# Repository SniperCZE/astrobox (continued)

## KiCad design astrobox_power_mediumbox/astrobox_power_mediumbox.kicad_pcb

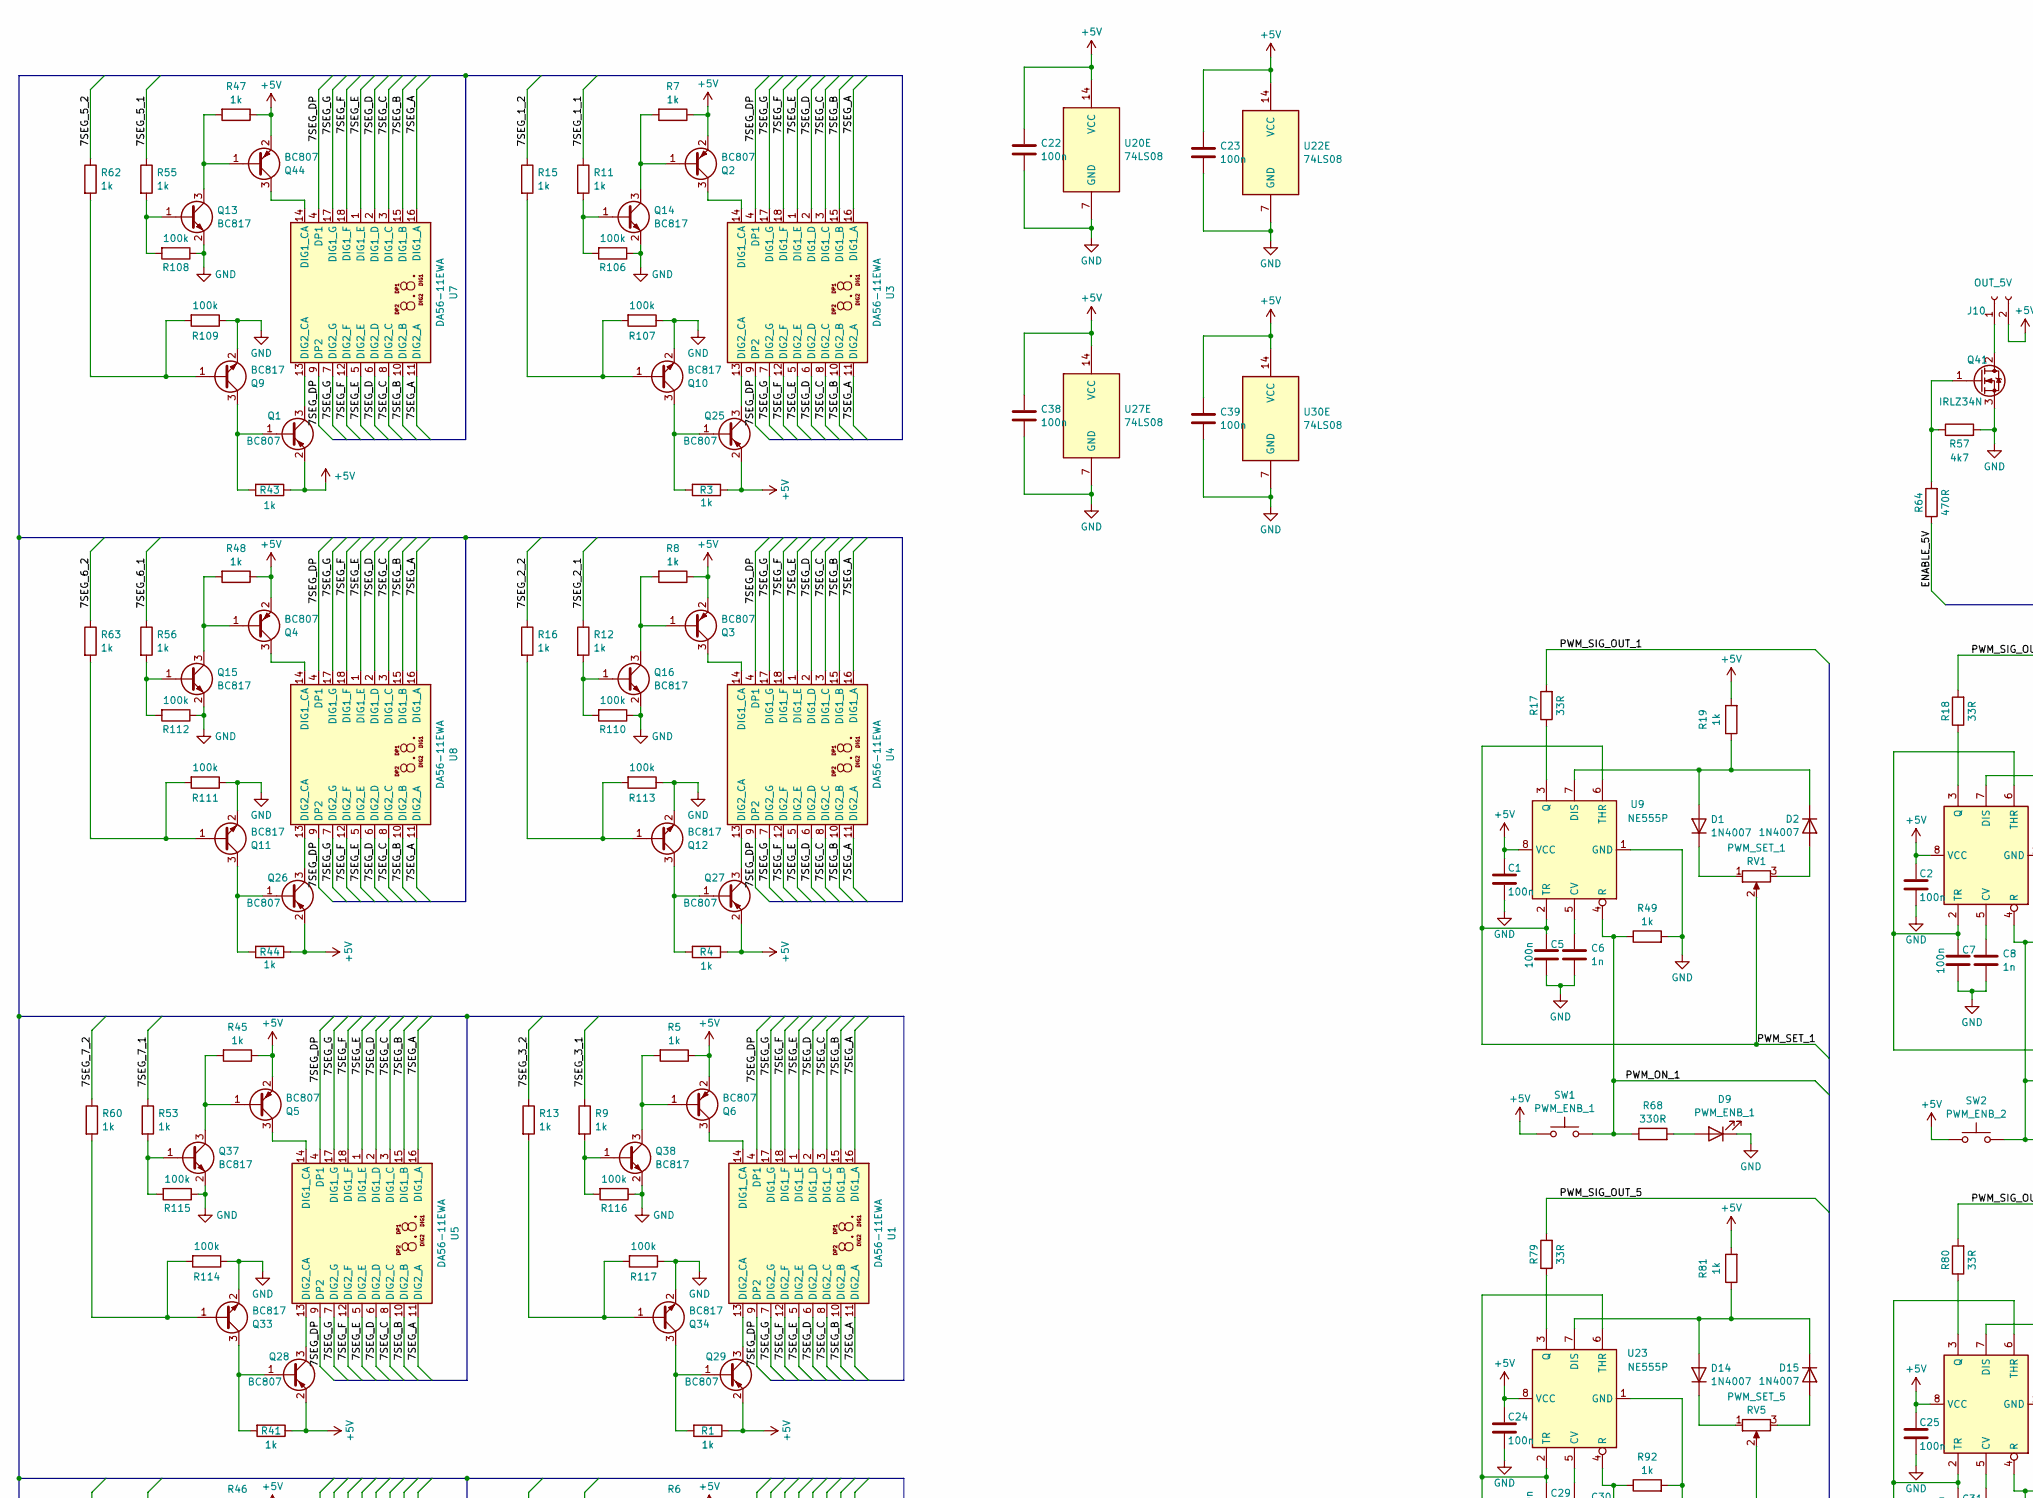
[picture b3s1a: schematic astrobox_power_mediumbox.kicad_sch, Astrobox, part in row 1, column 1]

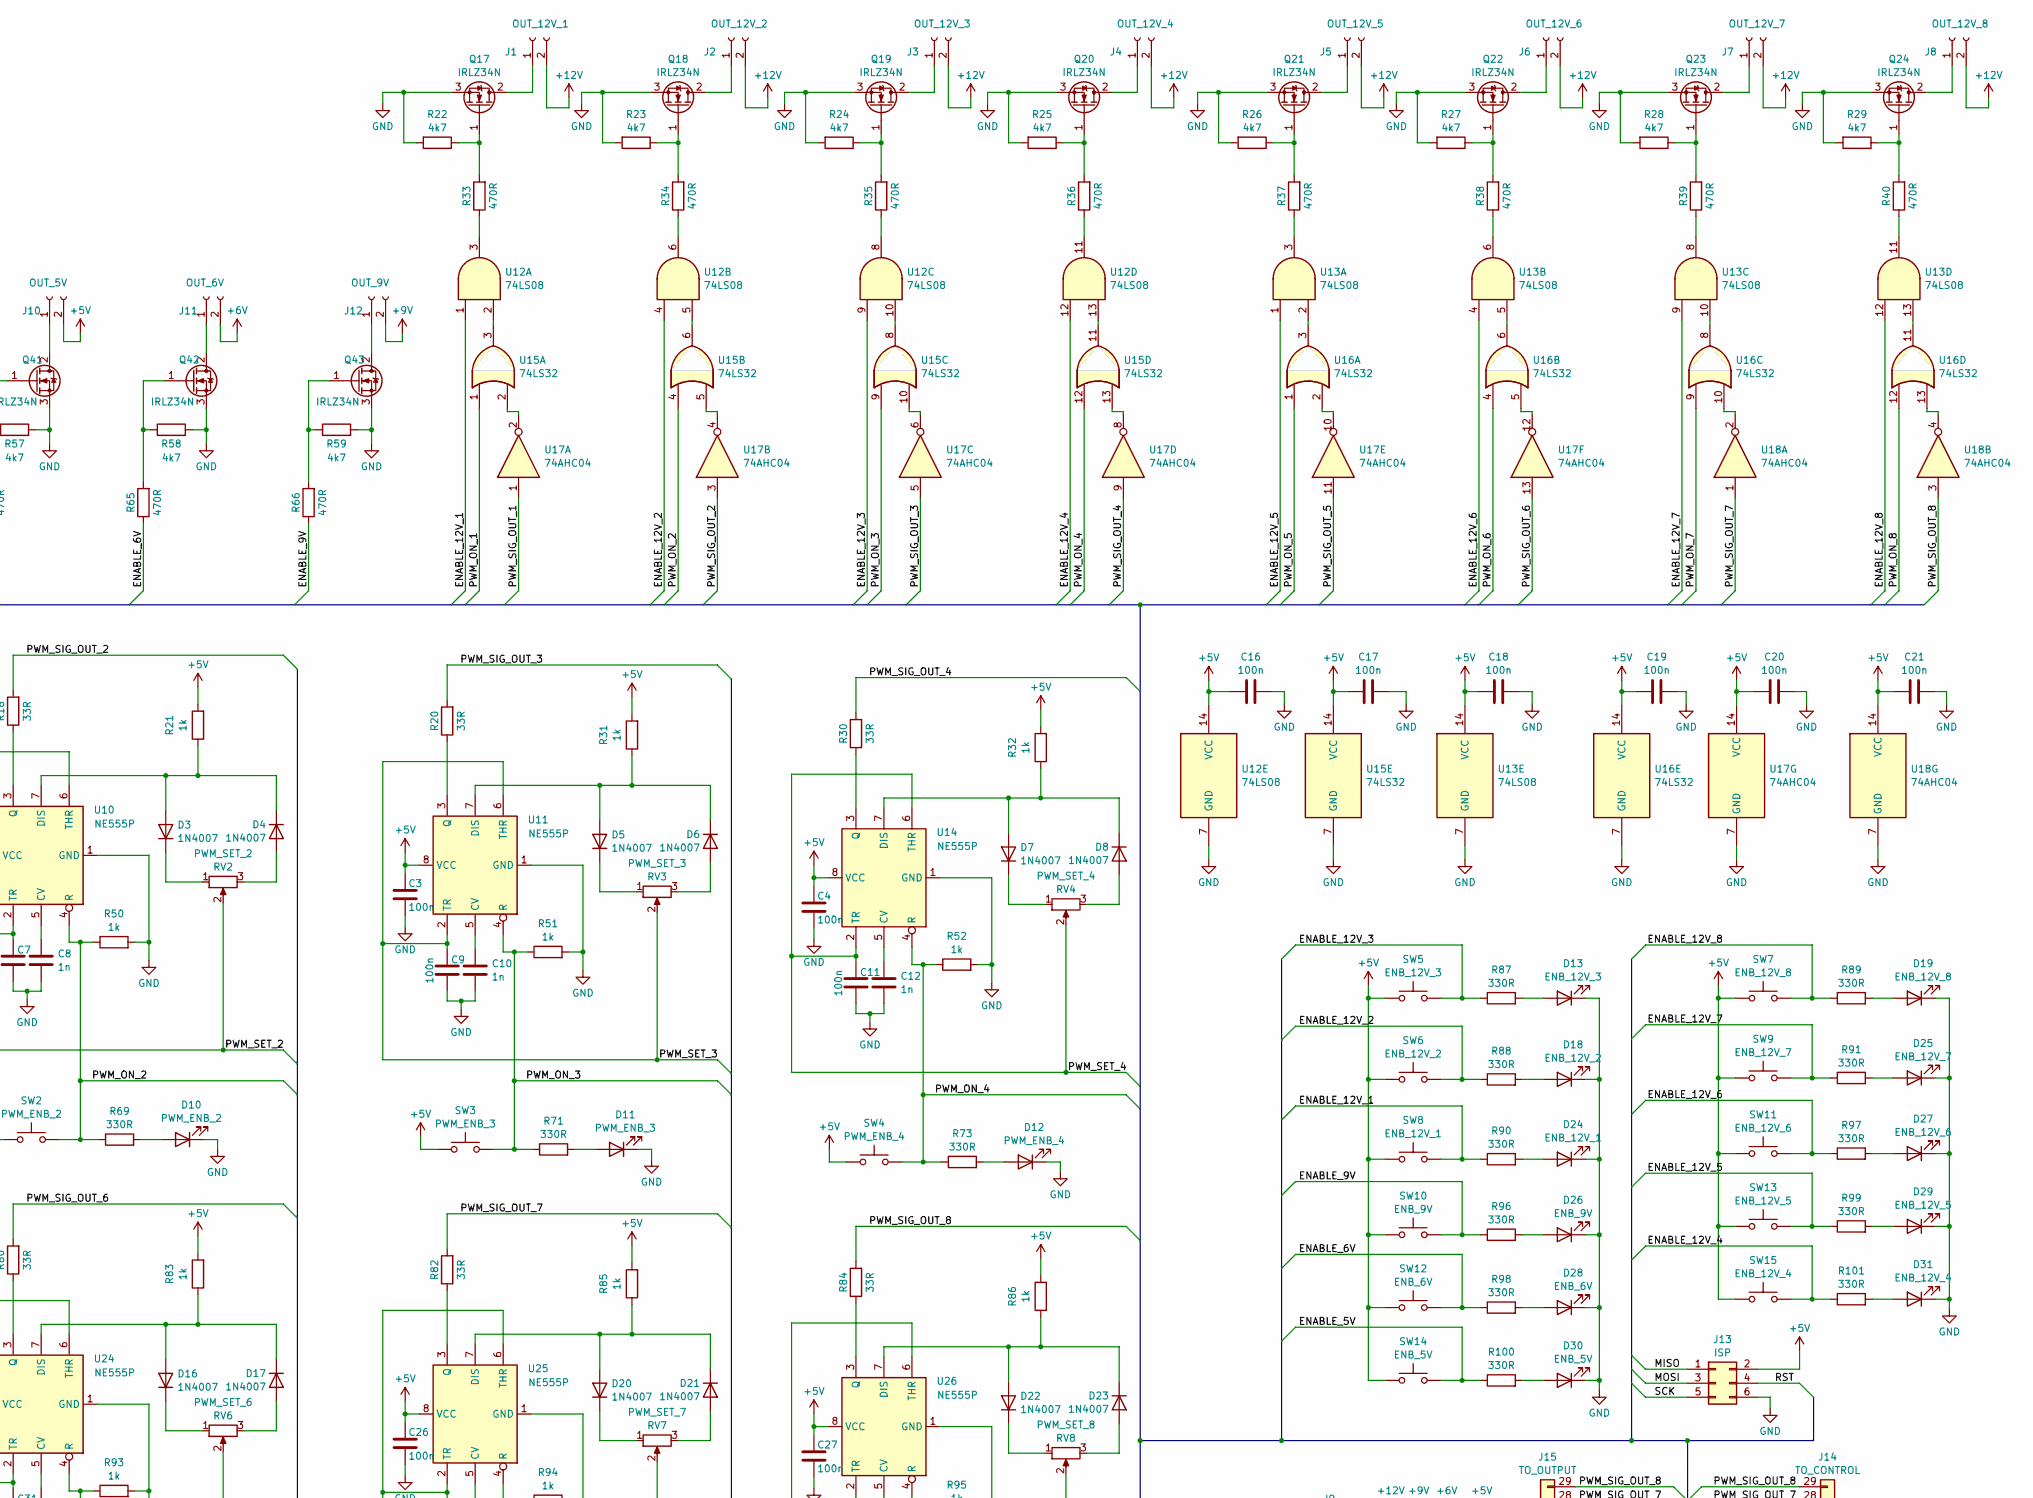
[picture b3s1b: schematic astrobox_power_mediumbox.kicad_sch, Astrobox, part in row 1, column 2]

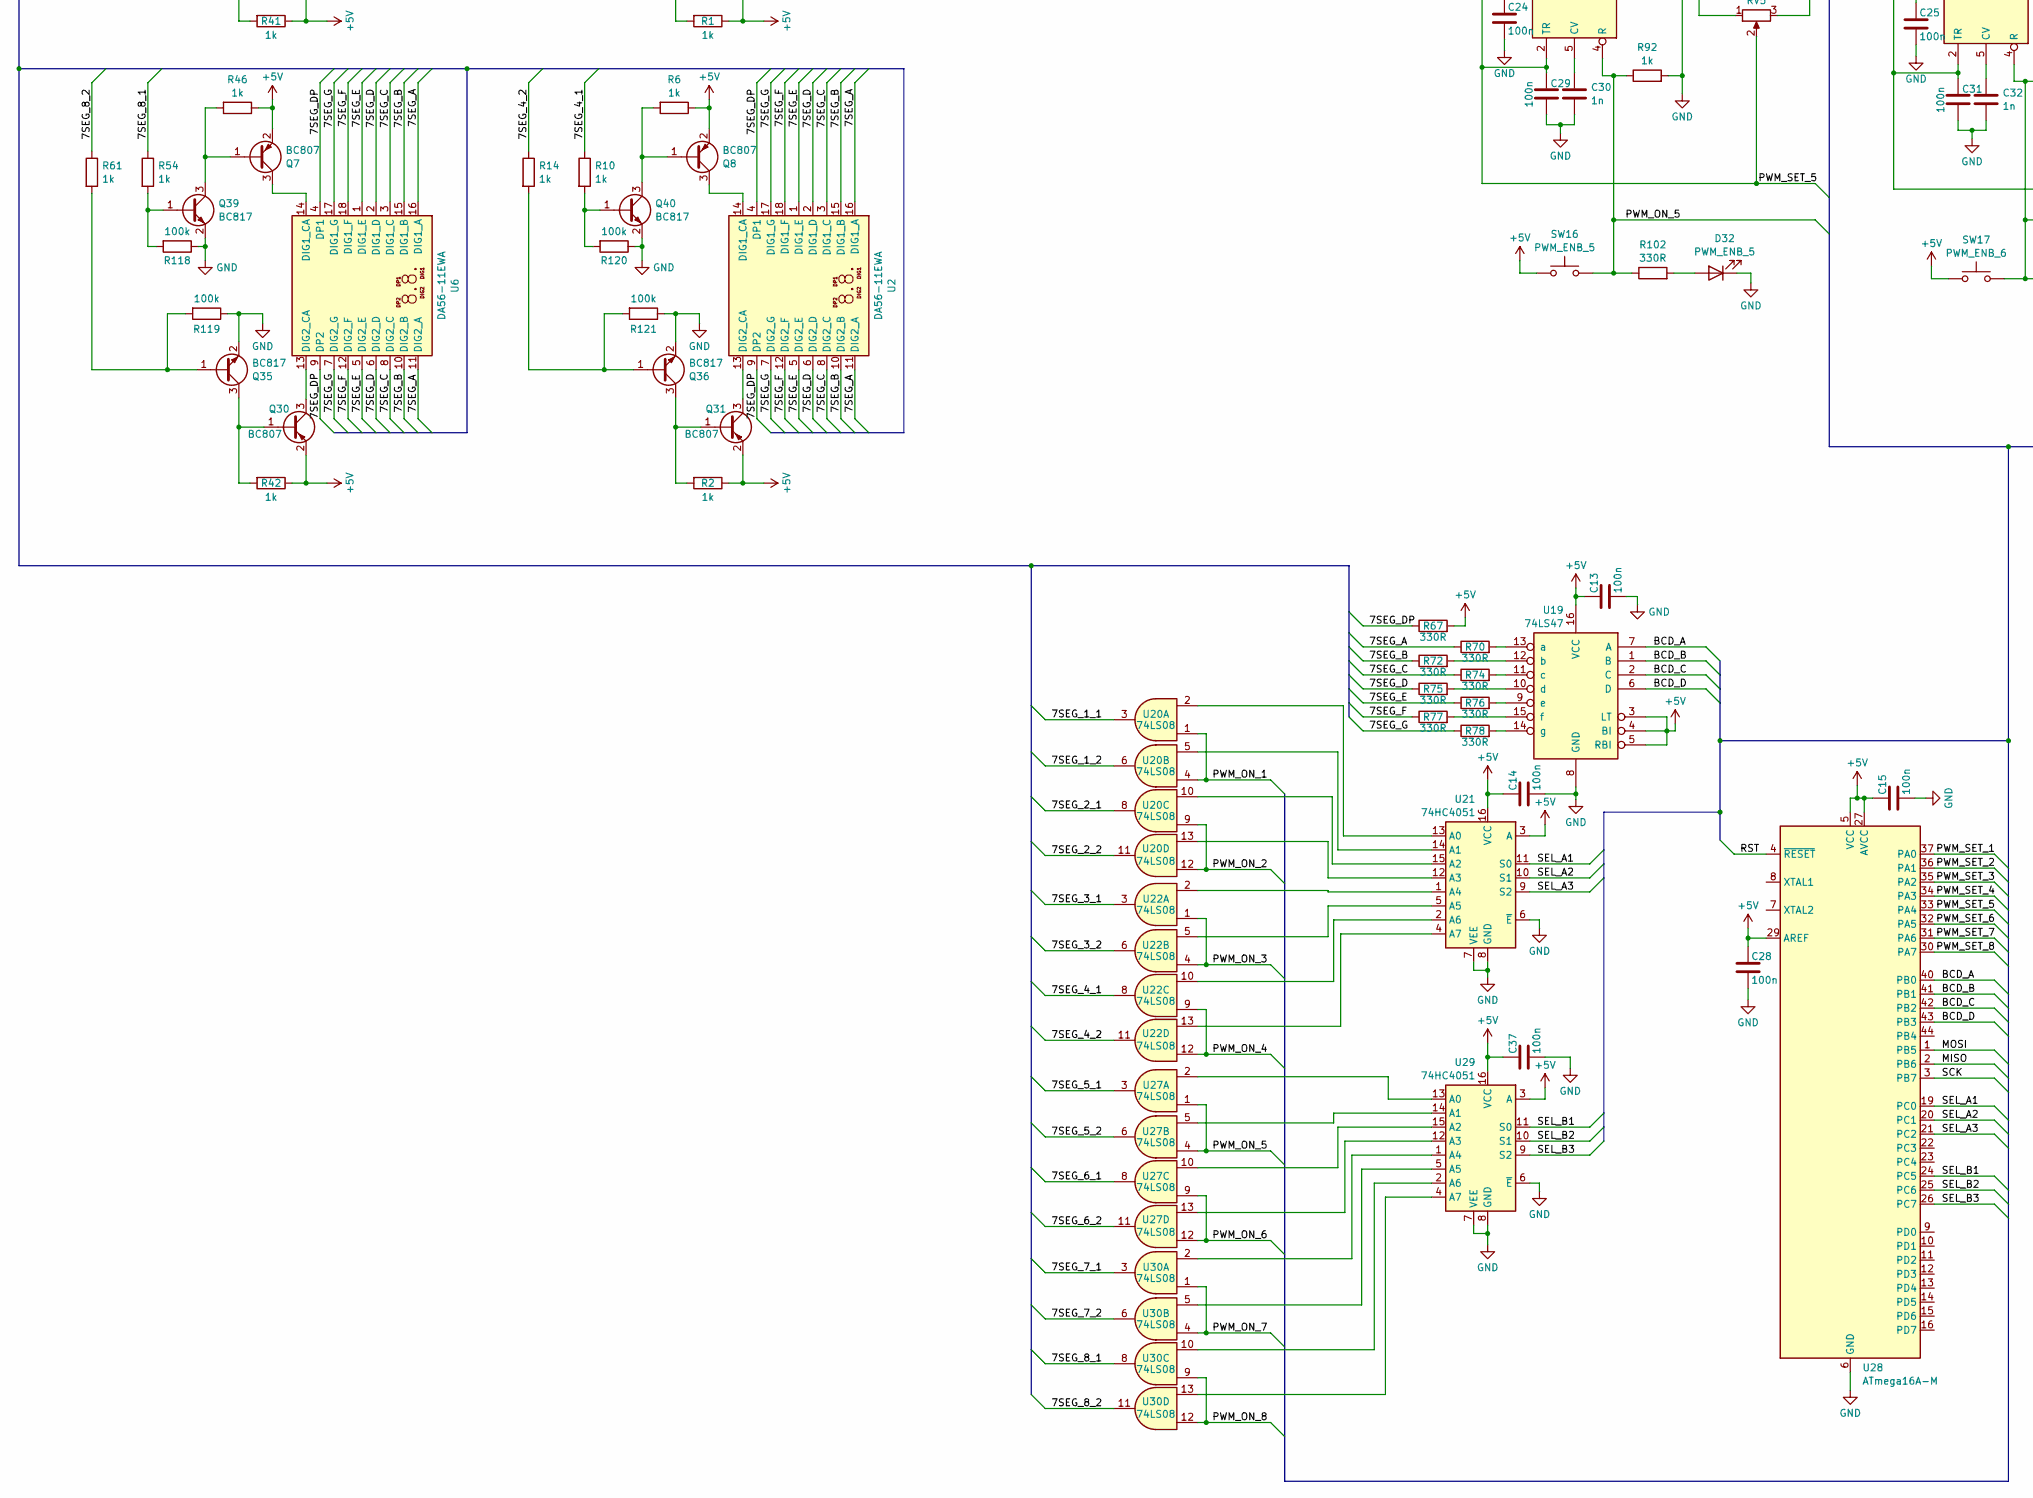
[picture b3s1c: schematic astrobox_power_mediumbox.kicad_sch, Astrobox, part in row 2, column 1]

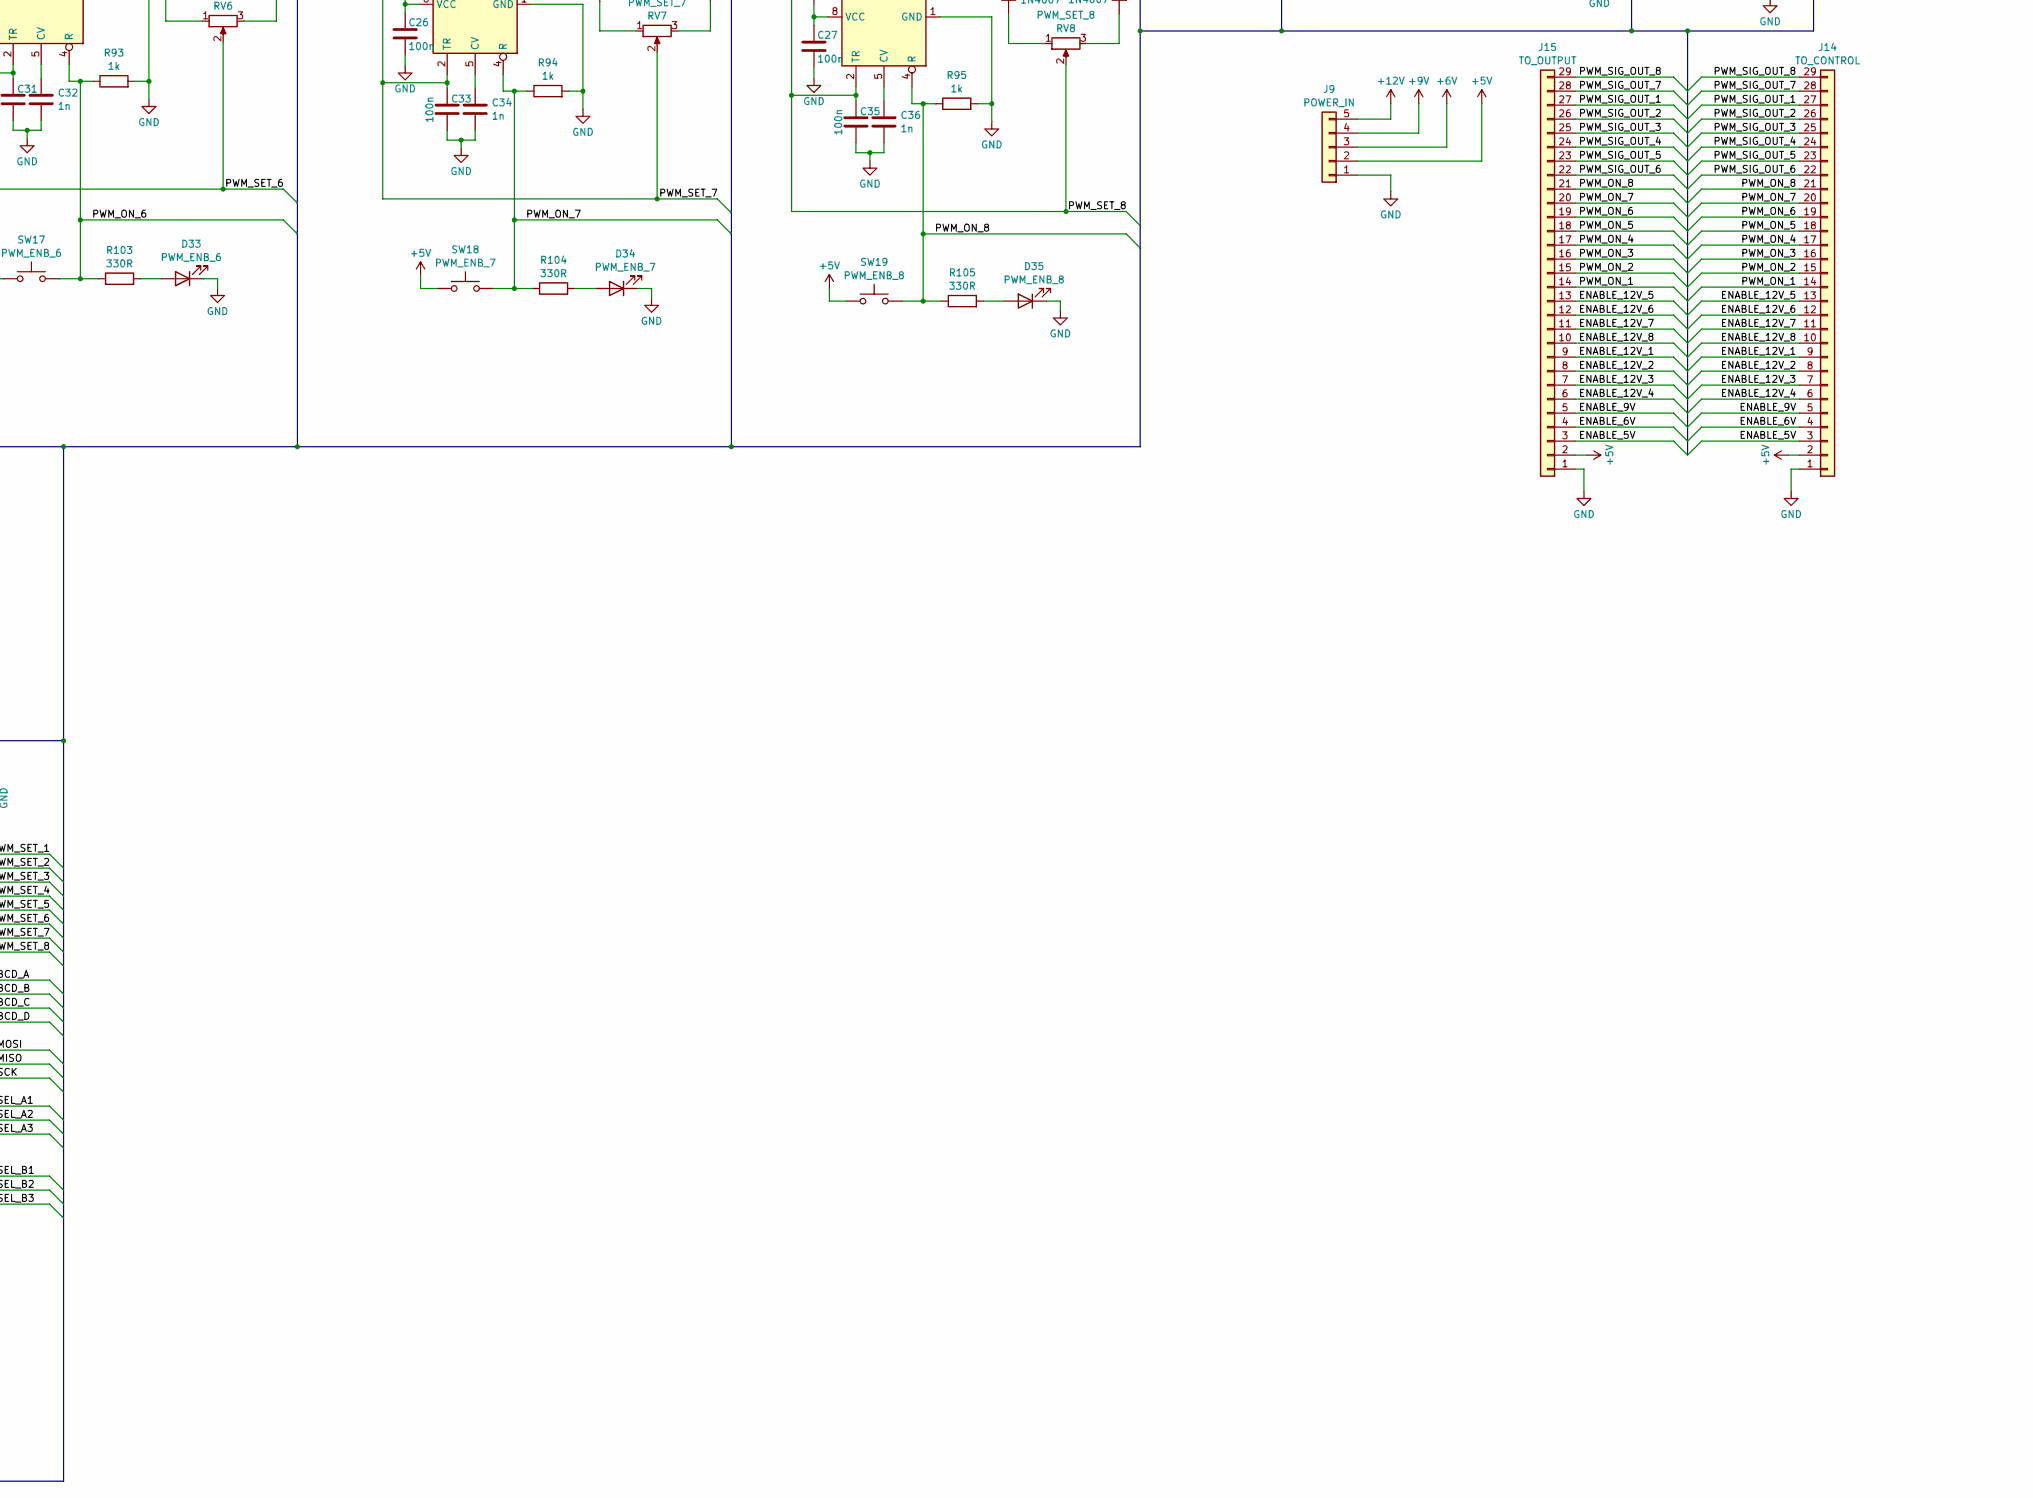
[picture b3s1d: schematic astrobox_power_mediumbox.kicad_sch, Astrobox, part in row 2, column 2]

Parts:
C1, C2, C3, C4, C5, C7, C9, C11, C13, C14, C15, C16, C17, C18, C19, C20, C21, C22, C23, C24, C25, C26, C27, C28, C29, C31, C33, C35, C37, C38, C39: 100n; C_1206_3216Metric_Pad1.33x1.80mm_HandSolder
C6, C8, C10, C12, C30, C32, C34, C36: 1n; C_1206_3216Metric_Pad1.33x1.80mm_HandSolder
D1, D2, D3, D4, D5, D6, D7, D8, D14, D15, D16, D17, D20, D21, D22, D23: 1N4007; D_SMA-SMB_Universal_Handsoldering
D9: PWM_ENB_1; LED_D5.0mm
D10: PWM_ENB_2; LED_D5.0mm
D11: PWM_ENB_3; LED_D5.0mm
D12: PWM_ENB_4; LED_D5.0mm
D13: ENB_12V_3; LED_D5.0mm
D18: ENB_12V_2; LED_D5.0mm
D19: ENB_12V_8; LED_D5.0mm
D24: ENB_12V_1; LED_D5.0mm
D25: ENB_12V_7; LED_D5.0mm
D26: ENB_9V; LED_D5.0mm
D27: ENB_12V_6; LED_D5.0mm
D28: ENB_6V; LED_D5.0mm
D29: ENB_12V_5; LED_D5.0mm
D30: ENB_5V; LED_D5.0mm
D31: ENB_12V_4; LED_D5.0mm
D32: PWM_ENB_5; LED_D5.0mm
D33: PWM_ENB_6; LED_D5.0mm
D34: PWM_ENB_7; LED_D5.0mm
D35: PWM_ENB_8; LED_D5.0mm
J1: OUT_12V_1; SolderWire-1.5sqmm_1x02_P6mm_D1.7mm_OD3mm
J2: OUT_12V_2; SolderWire-1.5sqmm_1x02_P6mm_D1.7mm_OD3mm
J3: OUT_12V_3; SolderWire-1.5sqmm_1x02_P6mm_D1.7mm_OD3mm
J4: OUT_12V_4; SolderWire-1.5sqmm_1x02_P6mm_D1.7mm_OD3mm
J5: OUT_12V_5; SolderWire-1.5sqmm_1x02_P6mm_D1.7mm_OD3mm
J6: OUT_12V_6; SolderWire-1.5sqmm_1x02_P6mm_D1.7mm_OD3mm
J7: OUT_12V_7; SolderWire-1.5sqmm_1x02_P6mm_D1.7mm_OD3mm
J8: OUT_12V_8; SolderWire-1.5sqmm_1x02_P6mm_D1.7mm_OD3mm
J9: POWER_IN; SolderWire-1.5sqmm_1x05_P6mm_D1.7mm_OD3mm
J10: OUT_5V; SolderWire-1.5sqmm_1x02_P6mm_D1.7mm_OD3mm
J11: OUT_6V; SolderWire-1.5sqmm_1x02_P6mm_D1.7mm_OD3mm
J12: OUT_9V; SolderWire-1.5sqmm_1x02_P6mm_D1.7mm_OD3mm
J13: ISP; PinHeader_2x03_P2.54mm_Vertical
J14: TO_CONTROL; PinHeader_1x29_P2.54mm_Vertical
J15: TO_OUTPUT; PinHeader_1x29_P2.54mm_Vertical
Q1, Q2, Q3, Q4, Q5, Q6, Q7, Q8, Q25, Q26, Q27, Q28, Q29, Q30, Q31, Q44: BC807; SOT-23_Handsoldering
Q9, Q10, Q11, Q12, Q13, Q14, Q15, Q16, Q33, Q34, Q35, Q36, Q37, Q38, Q39, Q40: BC817; SOT-23_Handsoldering
Q17, Q18, Q19, Q20, Q21, Q22, Q23, Q24, Q41, Q42, Q43: IRLZ34N; TO-220-3_Vertical
R1, R2, R3, R4, R5, R6, R7, R8, R9, R10, R11, R12, R13, R14, R15, R16, R19, R21, R31, R32, R41, R42, R43, R44, R45, R46, R47, R48, R49, R50, R51, R52, R53, R54, R55, R56, R60, R61, R62, R63, R81, R83, R85, R86, R92, R93, R94, R95: 1k; R_1206_3216Metric_Pad1.30x1.75mm_HandSolder
R17, R18, R20, R30, R79, R80, R82, R84: 33R; R_1206_3216Metric_Pad1.30x1.75mm_HandSolder
R22, R23, R24, R25, R26, R27, R28, R29, R57, R58, R59: 4k7; R_1206_3216Metric_Pad1.30x1.75mm_HandSolder
R33, R34, R35, R36, R37, R38, R39, R40, R64, R65, R66: 470R; R_1206_3216Metric_Pad1.30x1.75mm_HandSolder
R67, R68, R69, R70, R71, R72, R73, R74, R75, R76, R77, R78, R87, R88, R89, R90, R91, R96, R97, R98, R99, R100, R101, R102, R103, R104, R105: 330R; R_1206_3216Metric_Pad1.30x1.75mm_HandSolder
R106, R107, R108, R109, R110, R111, R112, R113, R114, R115, R116, R117, R118, R119, R120, R121: 100k; R_1206_3216Metric_Pad1.30x1.75mm_HandSolder
RV1: PWM_SET_1; SolderWire-1sqmm_1x03_P5.4mm_D1.4mm_OD2.7mm
RV2: PWM_SET_2; SolderWire-1sqmm_1x03_P5.4mm_D1.4mm_OD2.7mm
RV3: PWM_SET_3; SolderWire-1sqmm_1x03_P5.4mm_D1.4mm_OD2.7mm
RV4: PWM_SET_4; SolderWire-1sqmm_1x03_P5.4mm_D1.4mm_OD2.7mm
RV5: PWM_SET_5; SolderWire-1sqmm_1x03_P5.4mm_D1.4mm_OD2.7mm
RV6: PWM_SET_6; SolderWire-1sqmm_1x03_P5.4mm_D1.4mm_OD2.7mm
RV7: PWM_SET_7; SolderWire-1sqmm_1x03_P5.4mm_D1.4mm_OD2.7mm
RV8: PWM_SET_8; SolderWire-1sqmm_1x03_P5.4mm_D1.4mm_OD2.7mm
SW1: PWM_ENB_1; SolderWire-1sqmm_1x02_P5.4mm_D1.4mm_OD2.7mm
SW2: PWM_ENB_2; SolderWire-1sqmm_1x02_P5.4mm_D1.4mm_OD2.7mm
SW3: PWM_ENB_3; SolderWire-1sqmm_1x02_P5.4mm_D1.4mm_OD2.7mm
SW4: PWM_ENB_4; SolderWire-1sqmm_1x02_P5.4mm_D1.4mm_OD2.7mm
SW5: ENB_12V_3; SolderWire-1sqmm_1x02_P5.4mm_D1.4mm_OD2.7mm
SW6: ENB_12V_2; SolderWire-1sqmm_1x02_P5.4mm_D1.4mm_OD2.7mm
SW7: ENB_12V_8; SolderWire-1sqmm_1x02_P5.4mm_D1.4mm_OD2.7mm
SW8: ENB_12V_1; SolderWire-1sqmm_1x02_P5.4mm_D1.4mm_OD2.7mm
SW9: ENB_12V_7; SolderWire-1sqmm_1x02_P5.4mm_D1.4mm_OD2.7mm
SW10: ENB_9V; SolderWire-1sqmm_1x02_P5.4mm_D1.4mm_OD2.7mm
SW11: ENB_12V_6; SolderWire-1sqmm_1x02_P5.4mm_D1.4mm_OD2.7mm
SW12: ENB_6V; SolderWire-1sqmm_1x02_P5.4mm_D1.4mm_OD2.7mm
SW13: ENB_12V_5; SolderWire-1sqmm_1x02_P5.4mm_D1.4mm_OD2.7mm
SW14: ENB_5V; SolderWire-1sqmm_1x02_P5.4mm_D1.4mm_OD2.7mm
SW15: ENB_12V_4; SolderWire-1sqmm_1x02_P5.4mm_D1.4mm_OD2.7mm
SW16: PWM_ENB_5; SolderWire-1sqmm_1x02_P5.4mm_D1.4mm_OD2.7mm
SW17: PWM_ENB_6; SolderWire-1sqmm_1x02_P5.4mm_D1.4mm_OD2.7mm
SW18: PWM_ENB_7; SolderWire-1sqmm_1x02_P5.4mm_D1.4mm_OD2.7mm
SW19: PWM_ENB_8; SolderWire-1sqmm_1x02_P5.4mm_D1.4mm_OD2.7mm
U1, U2, U3, U4, U5, U6, U7, U8: DA56-11EWA; DA56-11SURKWA
U9, U10, U11, U14, U23, U24, U25, U26: NE555P; SOIC-8_5.3x6.2mm_P1.27mm
U12, U13, U20, U22, U27, U30: 74LS08; SO-14_3.9x8.65mm_P1.27mm
U15, U16: 74LS32; DIP-14_W7.62mm_Socket
U17, U18: 74AHC04; SO-14_3.9x8.65mm_P1.27mm
U19: 74LS47; DIP-16_W7.62mm_Socket
U21, U29: 74HC4051; SOIC-16_3.9x9.9mm_P1.27mm
U28: ATmega16A-M; TQFP-44-1EP_10x10mm_P0.8mm_EP4.5x4.5mm

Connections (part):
+5V: C1.1, C2.1, C3.1, C4.1, C13.1, C14.1, C15.1, C16.1, C17.1, C18.1, C19.1, C20.1, C21.1, C22.1, C23.1, C24.1, C25.1, C26.1, C27.1, C28.1, C37.1, C38.1, C39.1, J9.2, J10.2, J13.2, J14.2, J15.2, Q1.2 (E), Q2.2 (E), Q3.2 (E), Q4.2 (E), Q5.2 (E), Q6.2 (E), Q7.2 (E), Q8.2 (E), Q25.2 (E), Q26.2 (E), Q27.2 (E), Q28.2 (E), Q29.2 (E), Q30.2 (E), Q31.2 (E), Q44.2 (E), R1.1, R2.1, R3.1, R4.1, R5.1, R6.1, R7.1, R8.1, R19.2, R21.2, R31.2, R32.2, R41.1, R42.1, R43.1, R44.1, R45.1, R46.1, R47.1, R48.1, R67.2, R81.2, R83.2, R85.2, R86.2, SW1.1, SW2.1, SW3.1, SW4.1, SW5.1, SW6.1, SW7.1, SW8.1, SW9.1, SW10.1, SW11.1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
+6V: J9.3, J11.2
+9V: J9.4, J12.2
+12V: J1.2, J2.2, J3.2, J4.2, J5.2, J6.2, J7.2, J8.2, J9.5
/7SEG_1_1: R11.1, U20.3
/7SEG_1_2: R15.1, U20.6
/7SEG_2_1: R12.1, U20.8
/7SEG_2_2: R16.1, U20.11
/7SEG_3_1: R9.1, U22.3
/7SEG_3_2: R13.1, U22.6
/7SEG_4_1: R10.1, U22.8
/7SEG_4_2: R14.1, U22.11
/7SEG_5_1: R55.1, U27.3
/7SEG_5_2: R62.1, U27.6
/7SEG_6_1: R56.1, U27.8
/7SEG_6_2: R63.1, U27.11
/7SEG_7_1: R53.1, U30.3
/7SEG_7_2: R60.1, U30.6
/7SEG_8_1: R54.1, U30.8
/7SEG_8_2: R61.1, U30.11
/7SEG_A: R70.1, U1.11 (DIG2_A), U1.16 (DIG1_A), U2.11 (DIG2_A), U2.16 (DIG1_A), U3.11 (DIG2_A), U3.16 (DIG1_A), U4.11 (DIG2_A), U4.16 (DIG1_A), U5.11 (DIG2_A), U5.16 (DIG1_A), U6.11 (DIG2_A), U6.16 (DIG1_A), U7.11 (DIG2_A), U7.16 (DIG1_A), U8.11 (DIG2_A), U8.16 (DIG1_A)
/7SEG_B: R72.1, U1.10 (DIG2_B), U1.15 (DIG1_B), U2.10 (DIG2_B), U2.15 (DIG1_B), U3.10 (DIG2_B), U3.15 (DIG1_B), U4.10 (DIG2_B), U4.15 (DIG1_B), U5.10 (DIG2_B), U5.15 (DIG1_B), U6.10 (DIG2_B), U6.15 (DIG1_B), U7.10 (DIG2_B), U7.15 (DIG1_B), U8.10 (DIG2_B), U8.15 (DIG1_B)
/7SEG_C: R74.1, U1.3 (DIG1_C), U1.8 (DIG2_C), U2.3 (DIG1_C), U2.8 (DIG2_C), U3.3 (DIG1_C), U3.8 (DIG2_C), U4.3 (DIG1_C), U4.8 (DIG2_C), U5.3 (DIG1_C), U5.8 (DIG2_C), U6.3 (DIG1_C), U6.8 (DIG2_C), U7.3 (DIG1_C), U7.8 (DIG2_C), U8.3 (DIG1_C), U8.8 (DIG2_C)
/7SEG_D: R75.1, U1.2 (DIG1_D), U1.6 (DIG2_D), U2.2 (DIG1_D), U2.6 (DIG2_D), U3.2 (DIG1_D), U3.6 (DIG2_D), U4.2 (DIG1_D), U4.6 (DIG2_D), U5.2 (DIG1_D), U5.6 (DIG2_D), U6.2 (DIG1_D), U6.6 (DIG2_D), U7.2 (DIG1_D), U7.6 (DIG2_D), U8.2 (DIG1_D), U8.6 (DIG2_D)
/7SEG_DP: R67.1, U1.4 (DP1), U1.9 (DP2), U2.4 (DP1), U2.9 (DP2), U3.4 (DP1), U3.9 (DP2), U4.4 (DP1), U4.9 (DP2), U5.4 (DP1), U5.9 (DP2), U6.4 (DP1), U6.9 (DP2), U7.4 (DP1), U7.9 (DP2), U8.4 (DP1), U8.9 (DP2)
/7SEG_E: R76.1, U1.1 (DIG1_E), U1.5 (DIG2_E), U2.1 (DIG1_E), U2.5 (DIG2_E), U3.1 (DIG1_E), U3.5 (DIG2_E), U4.1 (DIG1_E), U4.5 (DIG2_E), U5.1 (DIG1_E), U5.5 (DIG2_E), U6.1 (DIG1_E), U6.5 (DIG2_E), U7.1 (DIG1_E), U7.5 (DIG2_E), U8.1 (DIG1_E), U8.5 (DIG2_E)
/7SEG_F: R77.1, U1.12 (DIG2_F), U1.18 (DIG1_F), U2.12 (DIG2_F), U2.18 (DIG1_F), U3.12 (DIG2_F), U3.18 (DIG1_F), U4.12 (DIG2_F), U4.18 (DIG1_F), U5.12 (DIG2_F), U5.18 (DIG1_F), U6.12 (DIG2_F), U6.18 (DIG1_F), U7.12 (DIG2_F), U7.18 (DIG1_F), U8.12 (DIG2_F), U8.18 (DIG1_F)
/7SEG_G: R78.1, U1.7 (DIG2_G), U1.17 (DIG1_G), U2.7 (DIG2_G), U2.17 (DIG1_G), U3.7 (DIG2_G), U3.17 (DIG1_G), U4.7 (DIG2_G), U4.17 (DIG1_G), U5.7 (DIG2_G), U5.17 (DIG1_G), U6.7 (DIG2_G), U6.17 (DIG1_G), U7.7 (DIG2_G), U7.17 (DIG1_G), U8.7 (DIG2_G), U8.17 (DIG1_G)
/BCD_A: U19.7 (A), U28.40 (PB0)
/BCD_B: U19.1 (B), U28.41 (PB1)
/BCD_C: U19.2 (C), U28.42 (PB2)
/BCD_D: U19.6 (D), U28.43 (PB3)
/ENABLE_5V: J14.3, J15.3, R64.1, R100.1, SW14.2
/ENABLE_6V: J14.4, J15.4, R65.1, R98.1, SW12.2
/ENABLE_9V: J14.5, J15.5, R66.1, R96.1, SW10.2
/ENABLE_12V_1: J14.9, J15.9, R90.1, SW8.2, U12.1
/ENABLE_12V_2: J14.8, J15.8, R88.1, SW6.2, U12.4
/ENABLE_12V_3: J14.7, J15.7, R87.1, SW5.2, U12.9
/ENABLE_12V_4: J14.6, J15.6, R101.1, SW15.2, U12.12
/ENABLE_12V_5: J14.13, J15.13, R99.1, SW13.2, U13.1
/ENABLE_12V_6: J14.12, J15.12, R97.1, SW11.2, U13.4
/ENABLE_12V_7: J14.11, J15.11, R91.1, SW9.2, U13.9
/ENABLE_12V_8: J14.10, J15.10, R89.1, SW7.2, U13.12
/MISO: J13.1, U28.2 (PB6)
/MOSI: J13.3, U28.1 (PB5)
/PWM_ON_1: J14.14, J15.14, R49.1, R68.1, SW1.2, U9.4 (R), U15.1, U20.1, U20.4
/PWM_ON_2: J14.15, J15.15, R50.1, R69.1, SW2.2, U10.4 (R), U15.4, U20.9, U20.12
/PWM_ON_3: J14.16, J15.16, R51.1, R71.1, SW3.2, U11.4 (R), U15.9, U22.1, U22.4
/PWM_ON_4: J14.17, J15.17, R52.1, R73.1, SW4.2, U14.4 (R), U15.12, U22.9, U22.12
/PWM_ON_5: J14.18, J15.18, R92.1, R102.1, SW16.2, U16.1, U23.4 (R), U27.1, U27.4
/PWM_ON_6: J14.19, J15.19, R93.1, R103.1, SW17.2, U16.4, U24.4 (R), U27.9, U27.12
/PWM_ON_7: J14.20, J15.20, R94.1, R104.1, SW18.2, U16.9, U25.4 (R), U30.1, U30.4
/PWM_ON_8: J14.21, J15.21, R95.1, R105.1, SW19.2, U16.12, U26.4 (R), U30.9, U30.12
/PWM_SET_1: C5.1, RV1.2, U9.2 (TR), U9.6 (THR), U28.37 (PA0)
/PWM_SET_2: C7.1, RV2.2, U10.2 (TR), U10.6 (THR), U28.36 (PA1)
/PWM_SET_3: C9.1, RV3.2, U11.2 (TR), U11.6 (THR), U28.35 (PA2)
/PWM_SET_4: C11.1, RV4.2, U14.2 (TR), U14.6 (THR), U28.34 (PA3)
/PWM_SET_5: C29.1, RV5.2, U23.2 (TR), U23.6 (THR), U28.33 (PA4)
/PWM_SET_6: C31.1, RV6.2, U24.2 (TR), U24.6 (THR), U28.32 (PA5)
/PWM_SET_7: C33.1, RV7.2, U25.2 (TR), U25.6 (THR), U28.31 (PA6)
/PWM_SET_8: C35.1, RV8.2, U26.2 (TR), U26.6 (THR), U28.30 (PA7)
/PWM_SIG_OUT_1: J14.27, J15.27, R17.2, U17.1
/PWM_SIG_OUT_2: J14.26, J15.26, R18.2, U17.3
/PWM_SIG_OUT_3: J14.25, J15.25, R20.2, U17.5
/PWM_SIG_OUT_4: J14.24, J15.24, R30.2, U17.9
/PWM_SIG_OUT_5: J14.23, J15.23, R79.2, U17.11
/PWM_SIG_OUT_6: J14.22, J15.22, R80.2, U17.13
/PWM_SIG_OUT_7: J14.28, J15.28, R82.2, U18.1
/PWM_SIG_OUT_8: J14.29, J15.29, R84.2, U18.3
/RST: J13.4, U28.4 (~RESET)
/SCK: J13.5, U28.3 (PB7)
/SEL_A1: U21.11 (S0), U28.19 (PC0)
/SEL_A2: U21.10 (S1), U28.20 (PC1)
/SEL_A3: U21.9 (S2), U28.21 (PC2)
/SEL_B1: U28.24 (PC5), U29.11 (S0)
/SEL_B2: U28.25 (PC6), U29.10 (S1)
/SEL_B3: U28.26 (PC7), U29.9 (S2)
GND: C1.2, C2.2, C3.2, C4.2, C5.2, C6.2, C7.2, C8.2, C9.2, C10.2, C11.2, C12.2, C13.2, C14.2, C15.2, C16.2, C17.2, C18.2, C19.2, C20.2, C21.2, C22.2, C23.2, C24.2, C25.2, C26.2, C27.2, C28.2, C29.2, C30.2, C31.2, C32.2, C33.2, C34.2, C35.2, C36.2, C37.2, C38.2, C39.2, D9.1 (K), D10.1 (K), D11.1 (K), D12.1 (K), D13.1 (K), D18.1 (K), D19.1 (K), D24.1 (K), D25.1 (K), D26.1 (K), D27.1 (K), D28.1 (K), D29.1 (K), D30.1 (K), D31.1 (K), D32.1 (K), D33.1 (K), D34.1 (K), D35.1 (K), J9.1, J13.6, J14.1, J15.1, Q9.2 (E), Q10.2 (E), Q11.2 (E), Q12.2 (E), Q13.2 (E), Q14.2 (E), Q15.2 (E), Q16.2 (E), Q17.3 (S), Q18.3 (S), Q19.3 (S), Q20.3 (S), Q21.3 (S), Q22.3 (S), Q23.3 (S), Q24.3 (S), Q33.2 (E), Q34.2 (E)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
unnamed: D1.2 (A), D2.1 (K), R19.1, U9.7 (DIS)
unnamed: D1.1 (K), RV1.1
unnamed: D2.2 (A), RV1.3
unnamed: D3.2 (A), D4.1 (K), R21.1, U10.7 (DIS)
unnamed: D3.1 (K), RV2.1
unnamed: D4.2 (A), RV2.3
unnamed: D5.2 (A), D6.1 (K), R31.1, U11.7 (DIS)
unnamed: D5.1 (K), RV3.1
unnamed: D6.2 (A), RV3.3
unnamed: D7.2 (A), D8.1 (K), R32.1, U14.7 (DIS)
unnamed: D7.1 (K), RV4.1
unnamed: D8.2 (A), RV4.3
unnamed: D9.2 (A), R68.2
unnamed: D10.2 (A), R69.2
unnamed: D11.2 (A), R71.2
unnamed: D12.2 (A), R73.2
unnamed: D13.2 (A), R87.2
unnamed: D14.2 (A), D15.1 (K), R81.1, U23.7 (DIS)
unnamed: D14.1 (K), RV5.1
unnamed: D15.2 (A), RV5.3
unnamed: D16.2 (A), D17.1 (K), R83.1, U24.7 (DIS)
unnamed: D16.1 (K), RV6.1
unnamed: D17.2 (A), RV6.3
unnamed: D18.2 (A), R88.2
unnamed: D19.2 (A), R89.2
unnamed: D20.2 (A), D21.1 (K), R85.1, U25.7 (DIS)
unnamed: D20.1 (K), RV7.1
unnamed: D21.2 (A), RV7.3
unnamed: D22.2 (A), D23.1 (K), R86.1, U26.7 (DIS)
unnamed: D22.1 (K), RV8.1
unnamed: D23.2 (A), RV8.3
unnamed: D24.2 (A), R90.2
unnamed: D25.2 (A), R91.2
unnamed: D26.2 (A), R96.2
unnamed: D27.2 (A), R97.2
unnamed: D28.2 (A), R98.2
unnamed: D29.2 (A), R99.2
unnamed: D30.2 (A), R100.2
unnamed: D31.2 (A), R101.2
unnamed: D32.2 (A), R102.2
unnamed: D33.2 (A), R103.2
unnamed: D34.2 (A), R104.2
unnamed: D35.2 (A), R105.2
unnamed: J1.1, Q17.2 (D)
unnamed: J2.1, Q18.2 (D)
unnamed: J3.1, Q19.2 (D)
unnamed: J4.1, Q20.2 (D)
unnamed: J5.1, Q21.2 (D)
unnamed: J6.1, Q22.2 (D)
unnamed: J7.1, Q23.2 (D)
unnamed: J8.1, Q24.2 (D)
unnamed: J10.1, Q41.2 (D)
unnamed: J11.1, Q42.2 (D)
unnamed: J12.1, Q43.2 (D)
unnamed: Q1.1 (B), Q9.3 (C), R43.2
unnamed: Q1.3 (C), U7.13 (DIG2_CA)
unnamed: Q2.3 (C), U3.14 (DIG1_CA)
unnamed: Q3.3 (C), U4.14 (DIG1_CA)
unnamed: Q4.3 (C), U8.14 (DIG1_CA)
unnamed: Q5.3 (C), U5.14 (DIG1_CA)
unnamed: Q6.3 (C), U1.14 (DIG1_CA)
unnamed: Q7.3 (C), U6.14 (DIG1_CA)
unnamed: Q8.3 (C), U2.14 (DIG1_CA)
unnamed: Q9.1 (B), R62.2, R109.2
unnamed: Q10.1 (B), R15.2, R107.2
unnamed: Q10.3 (C), Q25.1 (B), R3.2
unnamed: Q11.1 (B), R63.2, R111.2
unnamed: Q11.3 (C), Q26.1 (B), R44.2
unnamed: Q12.1 (B), R16.2, R113.2
unnamed: Q12.3 (C), Q27.1 (B), R4.2
unnamed: Q13.1 (B), R55.2, R108.2
unnamed: Q13.3 (C), Q44.1 (B), R47.2
unnamed: Q14.1 (B), R11.2, R106.2
unnamed: Q2.1 (B), Q14.3 (C), R7.2
unnamed: Q15.1 (B), R56.2, R112.2
unnamed: Q4.1 (B), Q15.3 (C), R48.2
unnamed: Q16.1 (B), R12.2, R110.2
unnamed: Q3.1 (B), Q16.3 (C), R8.2
unnamed: Q17.1 (G), R22.1, R33.2
unnamed: Q18.1 (G), R23.1, R34.2
unnamed: Q19.1 (G), R24.1, R35.2
unnamed: Q20.1 (G), R25.1, R36.2
unnamed: Q21.1 (G), R26.1, R37.2
unnamed: Q22.1 (G), R27.1, R38.2
unnamed: Q23.1 (G), R28.1, R39.2
unnamed: Q24.1 (G), R29.1, R40.2
unnamed: Q25.3 (C), U3.13 (DIG2_CA)
unnamed: Q26.3 (C), U8.13 (DIG2_CA)
unnamed: Q27.3 (C), U4.13 (DIG2_CA)
unnamed: Q28.1 (B), Q33.3 (C), R41.2
unnamed: Q28.3 (C), U5.13 (DIG2_CA)
unnamed: Q29.1 (B), Q34.3 (C), R1.2
unnamed: Q29.3 (C), U1.13 (DIG2_CA)
unnamed: Q30.1 (B), Q35.3 (C), R42.2
unnamed: Q30.3 (C), U6.13 (DIG2_CA)
unnamed: Q31.1 (B), Q36.3 (C), R2.2
unnamed: Q31.3 (C), U2.13 (DIG2_CA)
unnamed: Q33.1 (B), R60.2, R114.2
unnamed: Q34.1 (B), R13.2, R117.2
unnamed: Q35.1 (B), R61.2, R119.2
unnamed: Q36.1 (B), R14.2, R121.2
unnamed: Q37.1 (B), R53.2, R115.2
unnamed: Q5.1 (B), Q37.3 (C), R45.2
unnamed: Q38.1 (B), R9.2, R116.2
unnamed: Q6.1 (B), Q38.3 (C), R5.2
unnamed: Q39.1 (B), R54.2, R118.2
unnamed: Q7.1 (B), Q39.3 (C), R46.2
unnamed: Q40.1 (B), R10.2, R120.2
unnamed: Q8.1 (B), Q40.3 (C), R6.2
unnamed: Q41.1 (G), R57.1, R64.2
unnamed: Q42.1 (G), R58.1, R65.2
unnamed: Q43.1 (G), R59.1, R66.2
unnamed: Q44.3 (C), U7.14 (DIG1_CA)
unnamed: R33.1, U12.3
unnamed: R34.1, U12.6
unnamed: R35.1, U12.8
unnamed: R36.1, U12.11
unnamed: R37.1, U13.3
unnamed: R38.1, U13.6
unnamed: R39.1, U13.8
unnamed: R40.1, U13.11
unnamed: C6.1, U9.5 (CV)
unnamed: R17.1, U9.3 (Q)
unnamed: C8.1, U10.5 (CV)
unnamed: R18.1, U10.3 (Q)
unnamed: C10.1, U11.5 (CV)
unnamed: R20.1, U11.3 (Q)
unnamed: U12.2, U15.3
unnamed: U12.5, U15.6
unnamed: U12.10, U15.8
unnamed: U12.13, U15.11
unnamed: U13.2, U16.3
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
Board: 2 copper layers, 310 parts (0 on the bottom side), 254 nets, no tracks yet.

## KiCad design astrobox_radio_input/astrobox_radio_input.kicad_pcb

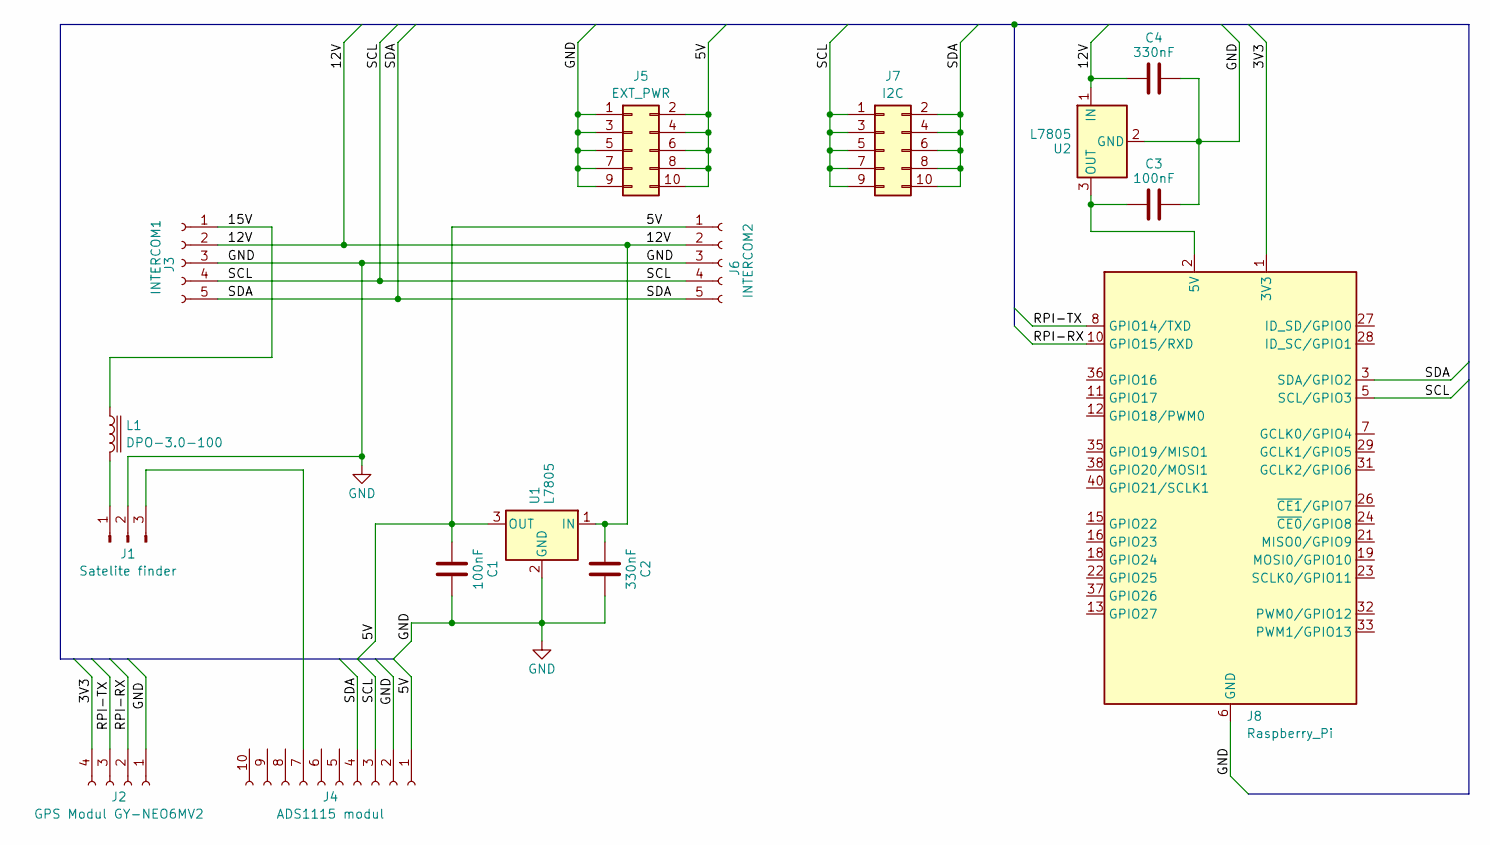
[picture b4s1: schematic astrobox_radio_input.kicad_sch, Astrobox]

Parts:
C1, C3: 100nF; C_Disc_D5.0mm_W2.5mm_P5.00mm
C2, C4: 330nF; C_Disc_D5.0mm_W2.5mm_P5.00mm
J1: Satelite finder; PinHeader_1x03_P2.54mm_Vertical
J2: GPS Modul GY-NEO6MV2; PinSocket_1x04_P2.54mm_Vertical
J3: INTERCOM1; JST_XH_B5B-XH-A_1x05_P2.50mm_Vertical
J4: ADS1115 modul; PinSocket_1x10_P2.54mm_Vertical
J5: EXT_PWR; PinHeader_2x05_P2.54mm_Vertical
J6: INTERCOM2; JST_XH_B5B-XH-A_1x05_P2.50mm_Vertical
J7: I2C; PinHeader_2x05_P2.54mm_Vertical
J8: Raspberry_Pi; PinHeader_2x20_P2.54mm_Vertical
L1: DPO-3.0-100; L_Toroid_Vertical_L25.4mm_W14.7mm_P12.20mm_Vishay_TJ5
U1, U2: L7805; TO-220-3_Vertical

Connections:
/3V3: J2.4, J8.1 (3V3), J8.17 (3V3)
/5V: C1.1, J4.1, J5.2, J5.4, J5.6, J5.8, J5.10, J6.1, U1.3 (OUT)
/12V: C2.2, C4.2, J3.2, J6.2, U1.1 (IN), U2.1 (IN)
/15V: J3.1, L1.1
/RPI-RX: J2.2, J8.10 (GPIO15/RXD)
/RPI-TX: J2.3, J8.8 (GPIO14/TXD)
/SCL: J3.4, J4.3, J6.4, J7.1, J7.3, J7.5, J7.7, J7.9, J8.5 (SCL/GPIO3)
/SDA: J3.5, J4.4, J6.5, J7.2, J7.4, J7.6, J7.8, J7.10, J8.3 (SDA/GPIO2)
GND: C1.2, C2.1, C3.2, C4.1, J1.2, J2.1, J3.3, J4.2, J5.1, J5.3, J5.5, J5.7, J5.9, J6.3, J8.6 (GND), J8.9 (GND), J8.14 (GND), J8.20 (GND), J8.25 (GND), J8.30 (GND), J8.34 (GND), J8.39 (GND), U1.2 (GND), U2.2 (GND)
unnamed: J1.1, L1.2
unnamed: J1.3, J4.7
unnamed: C3.1, J8.2 (5V), J8.4 (5V), U2.3 (OUT)
